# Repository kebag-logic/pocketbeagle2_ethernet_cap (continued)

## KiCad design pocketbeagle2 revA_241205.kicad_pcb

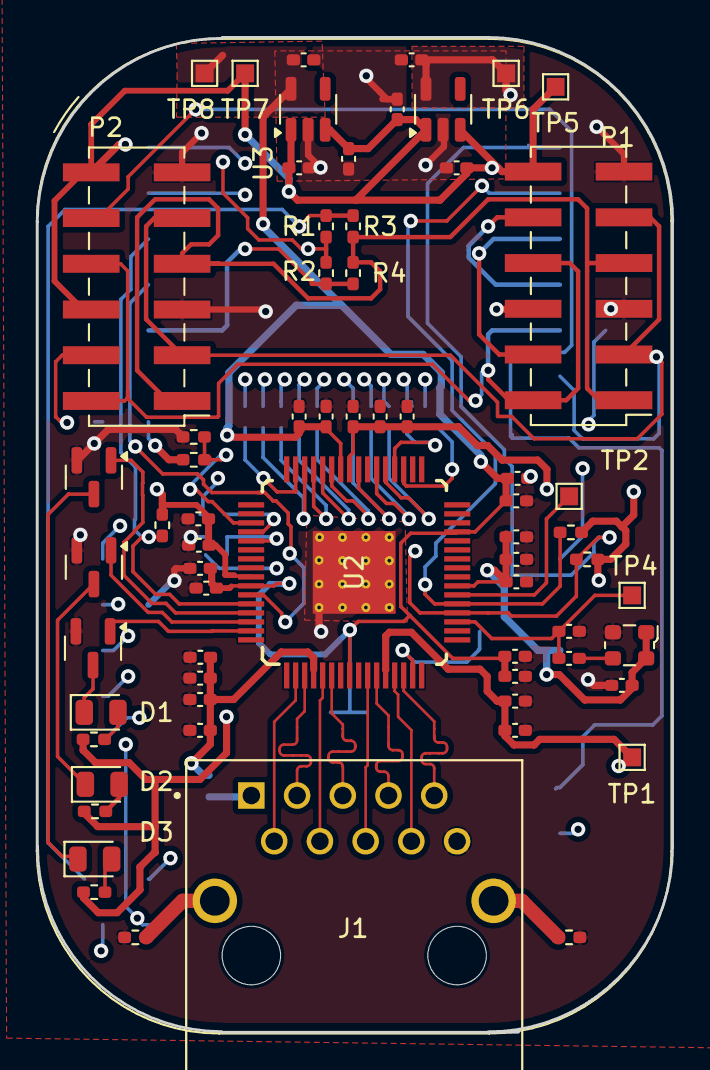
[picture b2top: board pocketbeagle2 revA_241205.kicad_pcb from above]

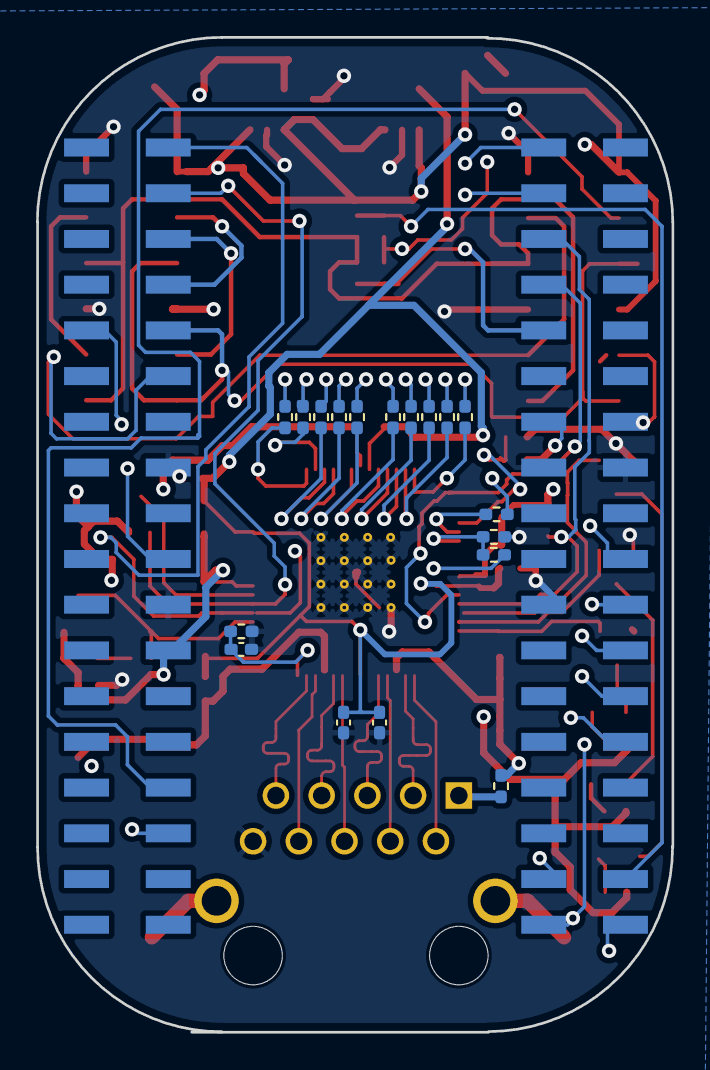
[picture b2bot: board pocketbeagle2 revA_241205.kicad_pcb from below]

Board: 4 copper layers, 35.3 x 55.3 mm, 84 parts (18 on the bottom side), 67 nets.

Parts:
C1, C2, C3, C4, C5, C6, C7, C9, C10, C13, C34, C35: 0.1uF; C_0402_1005Metric_Pad0.74x0.62mm_HandSolder
C8, C11, C12, C16, C17, C20, C21, C23, C25, C30, C31, C32, C33: 1uF; C_0402_1005Metric_Pad0.74x0.62mm_HandSolder
C14, C18: 27pf; C_0402_1005Metric_Pad0.74x0.62mm_HandSolder
C15, C22, C26: 10uF; C_0402_1005Metric_Pad0.74x0.62mm_HandSolder
C19, C24, C27: 0.01uF; C_0402_1005Metric_Pad0.74x0.62mm_HandSolder
C28: 22pF; C_0402_1005Metric_Pad0.74x0.62mm_HandSolder
D1: Green; LED_0805_2012Metric
D2: Orange; LED_0805_2012Metric
D3: Red; LED_0805_2012Metric
J1: 1840888-1; BEL_1840888-1
P1, P2: PMOD_I2S; PinHeader_2x06_P2.54mm_Vertical_SMD
Q1, Q2, Q3: BSS138; SOT-23
R1, R2, R3, R4, R26, R29: 0R; R_0402_1005Metric_Pad0.72x0.64mm_HandSolder
R5: 5K76; R_0402_1005Metric_Pad0.72x0.64mm_HandSolder
R6, R7: 2K49; R_0402_1005Metric_Pad0.72x0.64mm_HandSolder
R8, R9, R10, R11, R12, R13, R14, R15, R16, R17, R18, R19: 22R; R_0402_1005Metric_Pad0.72x0.64mm_HandSolder
R20, R21, R24: 2.2K; R_0402_1005Metric_Pad0.72x0.64mm_HandSolder
R22: 11K_1%; R_0402_1005Metric_Pad0.72x0.64mm_HandSolder
R23, R27, R28: 200R; R_0402_1005Metric_Pad0.72x0.64mm_HandSolder
R25: DNP; R_0402_1005Metric_Pad0.72x0.64mm_HandSolder
TP1, TP2, TP4, TP5, TP6, TP7, TP8: TestPoint; TestPoint_Pad_1.0x1.0mm
U1: PocketBeagle2; BeagleBoard_PocketBeagle
U2: DP83867IRPAPR; PAP0064M_N
U3, U4: TPS7A20; SOT-23-5
Y1: ECS-2520MV-xxx-xx; Oscillator_SMD_ECS_2520MV-xxx-xx-4Pin_2.5x2.0mm

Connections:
/Audio/MCLK: P1.1, P1.7, P2.1, P2.7, R3.2, R4.1
/Network/LED0: Q1.1 (G), U2.63 (LED_0)
/Network/LED1: Q2.1 (G), U2.62 (LED_1)
/Network/LED2: Q3.1 (G), U2.61 (LED_2)
/Network/MD0_N: J1.3 (MD0-), U2.3 (TD_M_A)
/Network/MD0_P: J1.2 (MD0+), U2.2 (TD_P_A)
/Network/MD1_N: J1.5 (MD1-), U2.6 (TD_M_B)
/Network/MD1_P: J1.4 (MD1+), U2.5 (TD_P_B)
/Network/MD2_N: J1.7 (MD2-), U2.11 (TD_M_C)
/Network/MD2_P: J1.6 (MD2+), U2.10 (TD_P_C)
/Network/MD3_N: J1.9 (MD3-), U2.14 (TD_M_D)
/Network/MD3_P: J1.8 (MD3+), U2.13 (TD_P_D)
/Network/RX_CTRL: R7.2, R12.2, U2.53 (RX_DV_RX_CTRL)
/Network/RX_D7: R5.1, R6.2, U2.51 (RX_D7_GPIO)
/Network/X_IN: C14.2, C18.2, TP4.1, U2.19 (XI)
BCLK: P1.3, P1.9, P2.3, P2.9, U1.47 (MCASP2.ACLKX)
GND: C1.2, C2.2, C3.2, C4.2, C5.2, C6.2, C7.2, C8.2, C9.2, C10.2, C11.2, C12.2, C13.2, C15.2, C16.2, C17.2, C18.1, C19.2, C20.2, C21.2, C22.2, C23.2, C24.2, C25.2, C26.2, C27.2, C28.2, C30.1, C31.2, C32.1, C33.2, C34.2, C35.2, J1.10 (GND), P1.5, P1.11, P2.5, P2.11, Q1.2 (S), Q2.2 (S), Q3.2 (S), R6.1, R7.1, R22.2, R26.1, R29.1, U1.15 (GND), U1.16 (GND), U1.22 (GND), U1.51 (GND), U1.57 (GND), U2.65 (GND), U2.V (NC), U3.2 (GND), U4.2 (GND), Y1.2 (GND)
INT_N/PWRDN_N: R24.2, U1.6 (SPI0.CS), U2.60 (INT_PWDN)
LRCK: P1.2, P1.8, P2.2, P2.8, U1.45 (MCASP2.AFSX)
MCLK_MCASP: R2.2, R4.2, U1.10 (EXT_REFCLK1)
MCLK_TIN: R1.2, R2.1, U1.36 (TIMER_IO0)
MCLK_TOUT: R1.1, R3.1, U1.33 (TIMER_IO1)
MDIO0_DIO: R21.1, U1.39 (GPIO23/MDIO0.IO), U2.21 (MDIO)
MDIO0_MDC: R20.1, U1.37 (MDIO0.MDC), U2.20 (MDC)
unnamed: D1.2 (A), R23.1
unnamed: D1.1 (K), Q1.3 (D)
unnamed: D2.2 (A), R27.1
unnamed: D2.1 (K), Q2.3 (D)
unnamed: D3.2 (A), R28.1
unnamed: D3.1 (K), Q3.3 (D)
unnamed: J1.S1 (SHIELD), R29.2
unnamed: J1.S2 (SHIELD__1), R26.2
unnamed: J1.1 (VCC), R25.1
unnamed: TP2.1, U2.22 (CLK_OUT)
unnamed: R14.2, U2.40 (GTX_CLK)
unnamed: C28.1, R22.1, U2.15 (RBIAS)
unnamed: R15.2, U2.43 (RX_CLK)
unnamed: R16.2, U2.44 (RX_D0)
unnamed: R17.2, U2.45 (RX_D1)
unnamed: R18.2, U2.46 (RX_D2)
unnamed: R19.2, U2.47 (RX_D3)
unnamed: R8.2, U2.38 (TX_D0)
unnamed: R9.2, U2.37 (TX_D1)
unnamed: R10.2, U2.36 (TX_D2)
unnamed: R11.2, U2.35 (TX_D3)
unnamed: R13.2, U2.52 (TX_EN_TX_CTRL)
unnamed: C14.1, Y1.3 (OUT)
PMOD1_SDIN: P1.4, U1.41 (MCASP2.AXR0)
PMOD1_SDOUT: P1.10, U1.43 (MCASP2.AXR1)
PMOD2.SDIN: P2.4, U1.13 (MCASP.AXR12)
PMOD2.SDOUT: P2.10, U1.65 (MCASP.AXR13)
RESET_N: U1.8 (SPI0.CLK), U2.59 (RESET_N)
RGMII_RD0: R16.1, U1.27 (AIN4(1.8V)/RGMII2_RD0)
RGMII_RD1: R17.1, U1.25 (AIN3(1.8V)/RGMII2_RD1)
RGMII_RD2: R18.1, U1.23 (AIN2(1.8V)/RGMII2_RD2)
RGMII_RD3: R19.1, U1.21 (AIN1(1.8V)/RGMII2_RD3)
RGMII_RX_CLK: R15.1, U1.34 (GPIO26/RGMII2_RXC)
RGMII_RX_CTRL: R12.1, U1.19 (AIN0(1.8V)/RGMII2_RXCTL)
RGMII_TD0: R8.1, U1.4 (GPIO89/RGMII2_TD0)
RGMII_TD1: R9.1, U1.67 (SPI1.CS/RGMII2_TD1)
RGMII_TD2: R10.1, U1.46 (GPIO52/RGMII2_TD2)
RGMII_TD3: R11.1, U1.55 (GPIO27/RGMII2_TD3)
RGMII_TX_CLK: R14.1, U1.35 (PRU1.10/RGMII2_TXC)
RGMII_TX_CTRL: R13.1, U1.2 (AIN6/GPIO87/RGMII2_TXCTL)
VDD_1V1: C3.1, C7.1, C10.1, C13.1, C17.1, C21.1, C23.1, C25.1, C26.1, C27.1, C31.1, TP8.1, U2.8 (VDD1P1), U2.29 (VDD1P1), U2.42 (VDD1P1), U2.58 (VDD1P1), U3.5 (OUT)
VDD_2V5: C1.1, C5.1, C8.1, C11.1, C15.1, C19.1, C33.1, R25.2, TP1.1, TP6.1, U2.4 (VDDA2P5), U2.12 (VDDA2P5), U4.5 (OUT)
VDD_3V3: C2.1, C4.1, C6.1, C9.1, C12.1, C16.1, C20.1, C22.1, C24.1, C30.2, C32.2, C34.1, C35.1, P1.6, P1.12, P2.6, P2.12, R5.2, R20.2, R21.2, R23.2, R24.1, R27.2, R28.2, TP5.1, TP7.1, U1.14 (3.3V), U1.59 (3.3V), U2.23 (VDDIO), U2.41 (VDDIO), U2.57 (VDDIO), U3.1 (IN), U3.3 (EN), U4.1 (IN), U4.3 (EN), Y1.1 (Tri-State), Y1.4 (VDD)

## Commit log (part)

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2025-08-22 Adding readme.md
2025-08-22 Do not provide the link to the pictures
2025-08-23 Updating pcb
2025-08-23 Preparing routing for RGMII and MDI interfaces
2025-08-23 MDIX routing done
2025-08-24 Fully routed PCB, missing fligth time matching on the RGMII
